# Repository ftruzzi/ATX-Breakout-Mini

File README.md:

ATX Breakout Board
=================

Eagle files for my ATX Breakout Board (v1, with USB support using a TPS2513 and voltage control with a LM317). Based on the Dangerous Prototypes' idea.

## New version (v1.2) ##

<p align="center">
  
</p>

Just finished updating the board. BOM updates and post blogs will follow. I'm also printing a second batch (20-30 PCBs) soon.

Changes and additions:

*   Thickened many traces, **removed pin headers** in the middle of the board and **added one behind each binding post** (up to 5 output pins per voltage line, with no risk of burning any traces).
*   **Added resistors to the USB ports (on the back of the board).** You may want to use them for USB identification, as they are cheaper and easier to find than the TPS2513. Adafruit link for more info: https://learn.adafruit.com/minty-boost/icharging
*   Moved LM317 so that you can mount it horizontally + used a footprint with longpads, should you want to solder wires to an external voltage reg + heatsink.
*   **Prototyping area added** at the top left of the board. Not sure if it will ever come useful, but I had some empty space there. You have easy access to the 3V3 and 5V lines.
*   Moved/rearranged several parts (pot, switch, LEDs) in order to draw shorter and cleaner traces.

##Features

*   **24-pin ATX** connector.
*   Voltage lines are all broken out individually on **binding posts**.
*   **LM317-based voltage regulator**. Using a 300 ohm resistor and a 2K ohm potentiometer, voltage range is 1.25-9V.
*   **2 USB ports **based on the TPS2513 from Texas Instruments. They can automatically detect what device is connected and adjust resistance on D+ and D- lines as needed. This means **full compatibility and maximum charging speed on both Apple and Android devices**. One of them is connected to 5v_STDBY, so that it works even when the PSU is off.
*   Pretty much everything can be **fused**. I left -12V out because it can only carry low amounts of current on most PSUs (mine is 500mA maximum).
*   **Breadboard pin headers** so that voltage lines can be connected to a breadboard using jumper cables.
*   **Voltmeter** headers in order to know the LM317 output voltage.
*   There is room for a **9W power resistor** is your PSU needs it to stabilize output voltages. You can connect it either to the 5v rail or to the 12v one by jumpering the corresponding pads.
*   **Status LEDs** on fused lines and USBs so you can check if everything works fine.
*   Screw holes for standoffs.

More details and pictures on my blog: http://b.truzzi.me/building-a-better-breakout-board-for-atx-psus-2

Suggestions and feedback are very welcome!

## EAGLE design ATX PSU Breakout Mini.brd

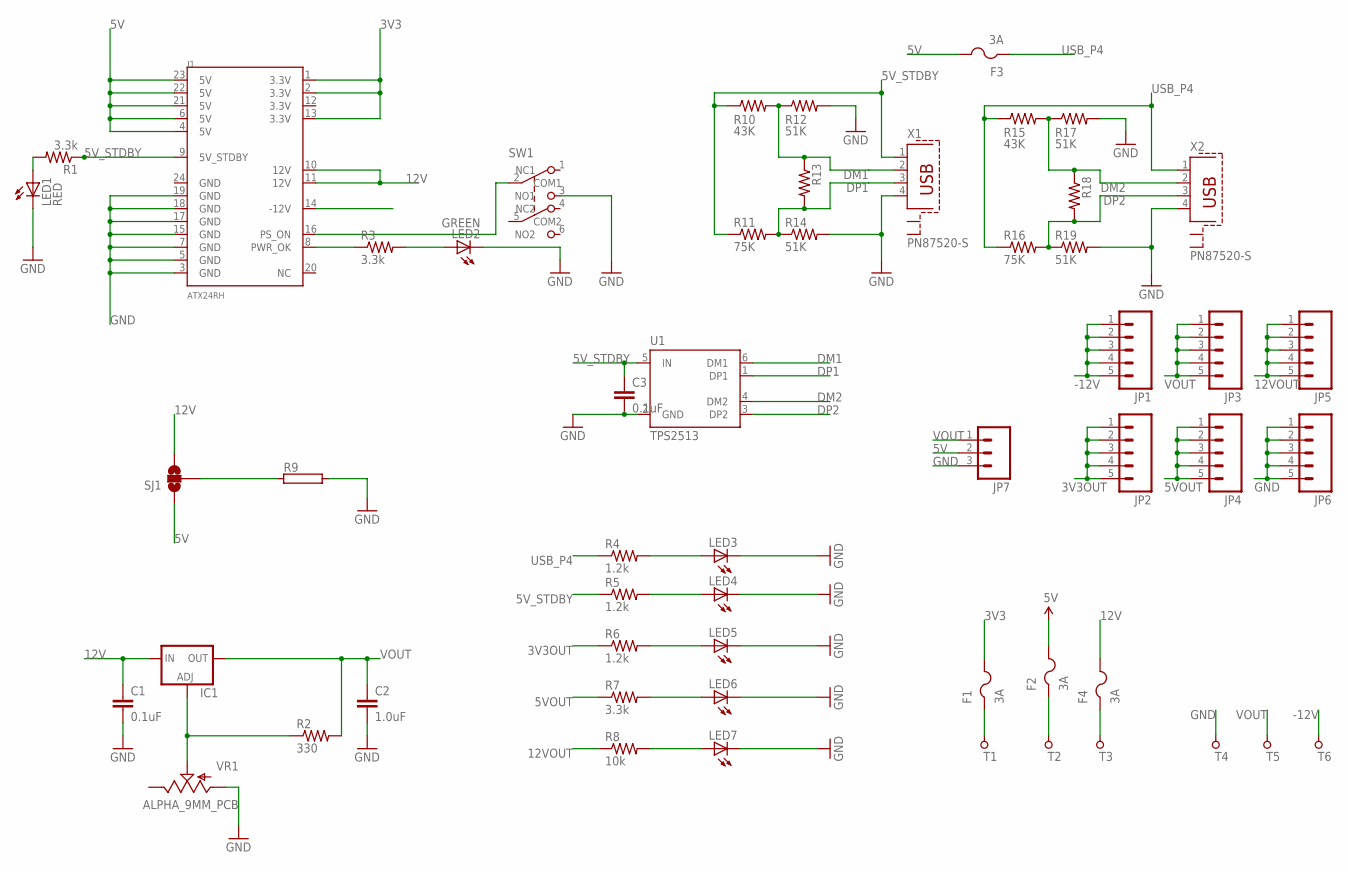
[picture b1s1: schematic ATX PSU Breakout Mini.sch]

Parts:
C1, C3: 0.1uF; 0805
C2: 1.0uF; 0805
F1, F2, F3, F4: 3A; 1812
IC1: LM317TL; 317TL
J1: ATX24RH; ATX24_RIGHT_ANGLE
JP1, JP2, JP3, JP4, JP5, JP6: M05PTH; 1X05
JP7: M03LOCK; 1X03_LOCK
LED1: RED; CHIPLED_0805
LED2: GREEN; CHIPLED_0805
LED3, LED4, LED5, LED6, LED7: LEDCHIPLED_0805; CHIPLED_0805
R1, R3, R7: 3.3k; 0805
R2: 330; 0805
R4, R5, R6: 1.2k; 0805
R8: 10k; 0805
R9: RKH214-8; KH214-8
R10, R15: 43K; 0805
R11, R16: 75K; 0805
R12, R14, R17, R19: 51K; 0805
R13, R18: RESISTOR0805-RES; 0805
SJ1: SOLDERJUMPER_2WAYS; SJ_3
SW1: SW_PUSH_DPDT; SW_PUSH_BUTTON_MINI
T1: 3V3; PAD_ROUND_4.1MM
T2: 5V; PAD_ROUND_4.1MM
T3: 12V; PAD_ROUND_4.1MM
T4: GND; PAD_ROUND_4.1MM
T5: ADJ; PAD_ROUND_4.1MM
T6: -12V; PAD_ROUND_4.1MM
U1: TPS2513; SOT23-6
VR1: ALPHA_9MM_PCB
X1, X2: PN87520-S

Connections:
3V3: F1.2, J1.1 (3.3V), J1.2 (3.3V), J1.13 (3.3V)
3V3OUT: F1.1, JP2.1, JP2.2, JP2.3, JP2.4, JP2.5, R6.1, T1.P
5V: F2.2, F3.2, J1.4 (5V), J1.6 (5V), J1.21 (5V), J1.22 (5V), J1.23 (5V), JP7.2, SJ1.1
5VOUT: F2.1, JP4.1, JP4.2, JP4.3, JP4.4, JP4.5, R7.1, T2.P
5V_STDBY: C3.1, J1.9 (5V_STDBY), R1.1, R5.1, R10.1, R11.1, U1.5 (IN), X1.1
12V: C1.1, F4.2, IC1.3 (IN), J1.10 (12V), J1.11 (12V), SJ1.3
12VOUT: F4.1, JP5.1, JP5.2, JP5.3, JP5.4, JP5.5, R8.1, T3.P
-12V: J1.14 (-12V), JP1.1, JP1.2, JP1.3, JP1.4, JP1.5, T6.P
DM1: R10.2, R12.1, R13.1, U1.6 (DM1), X1.2
DM2: R15.2, R17.1, R18.1, U1.4 (DM2), X2.2
DP1: R11.2, R13.2, R14.1, U1.1 (DP1), X1.3
DP2: R16.2, R18.2, R19.1, U1.3 (DP2), X2.3
GND: C1.2, C2.2, C3.2, J1.3 (GND), J1.5 (GND), J1.7 (GND), J1.15 (GND), J1.17 (GND), J1.18 (GND), J1.19 (GND), JP6.1, JP6.2, JP6.3, JP6.4, JP6.5, JP7.3, LED1.C, LED2.C, LED3.C, LED4.C, LED5.C, LED6.C, LED7.C, R9.2, R12.2, R14.2, R17.2, R19.2, SW1.3 (NO1), T4.P, U1.2 (GND), VR1.1 (A), X1.4, X2.4
unnamed: J1.8 (PWR_OK), R3.1
unnamed: LED2.A, R3.2
unnamed: R9.1, SJ1.2
unnamed: IC1.1 (ADJ), R2.1, VR1.2 (S)
unnamed: J1.16 (PS_ON), SW1.2 (COM1)
unnamed: LED1.A, R1.2
unnamed: LED4.A, R5.2
unnamed: LED3.A, R4.2
unnamed: LED5.A, R6.2
unnamed: LED6.A, R7.2
unnamed: LED7.A, R8.2
USB_P4: F3.1, R4.1, R15.1, R16.1, X2.1
VOUT: C2.1, IC1.2 (OUT), JP3.1, JP3.2, JP3.3, JP3.4, JP3.5, JP7.1, R2.2, T5.P

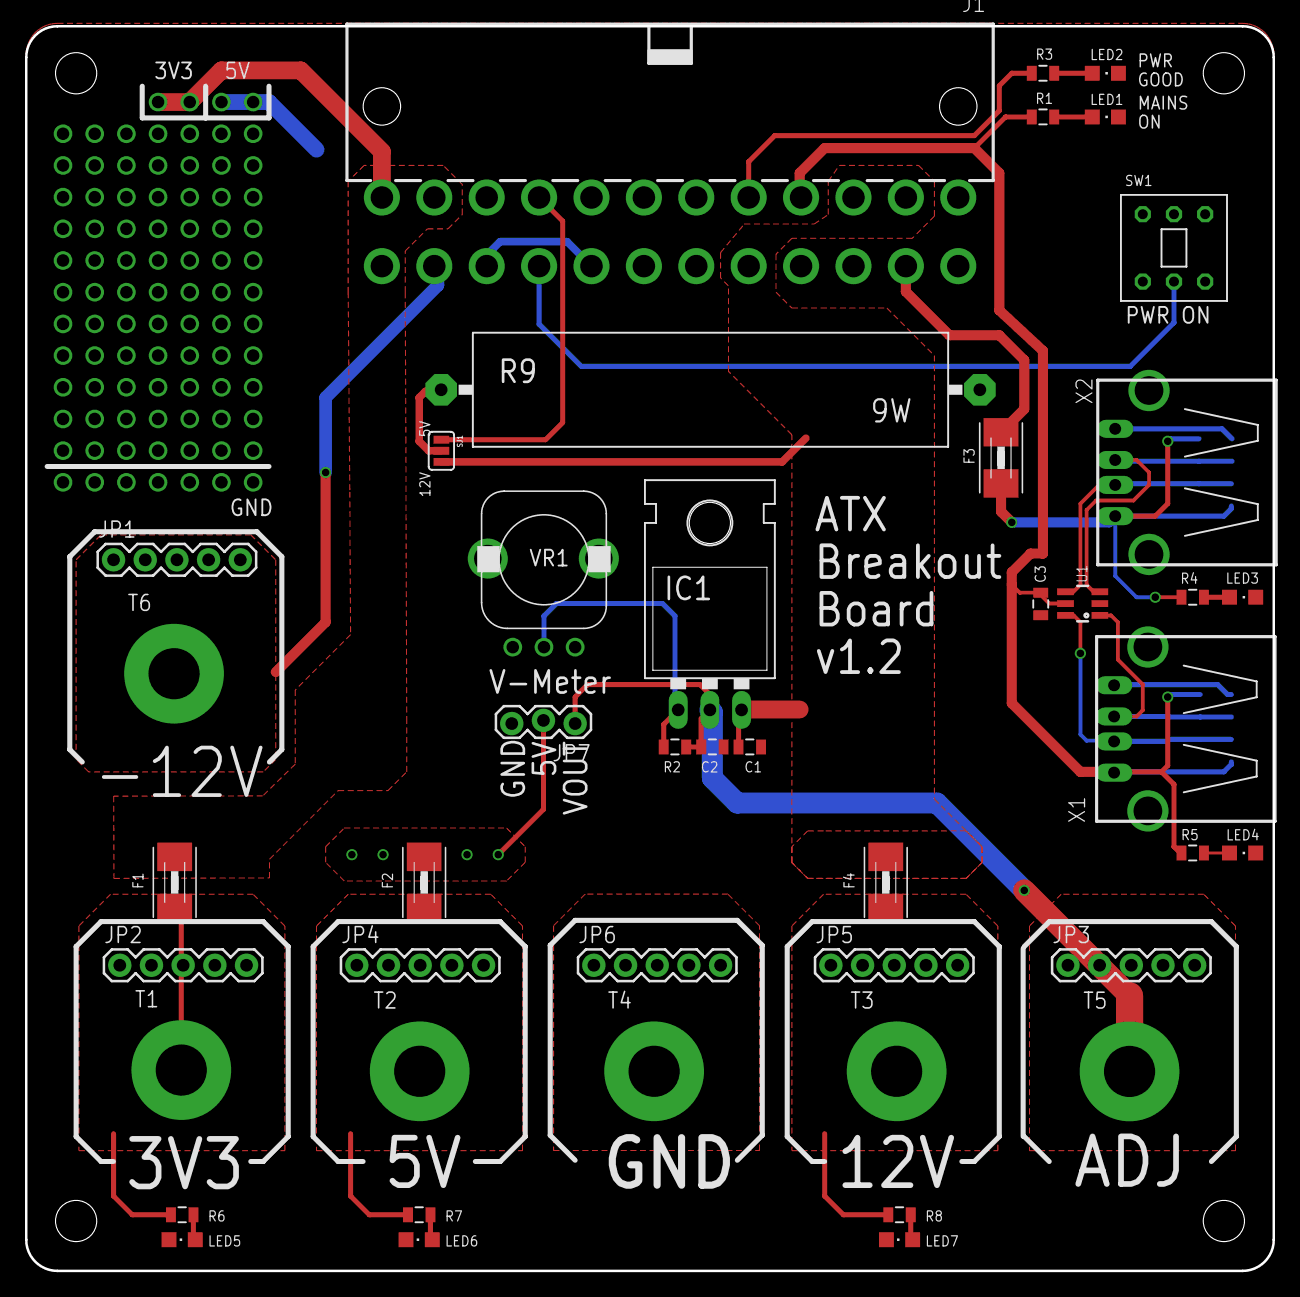
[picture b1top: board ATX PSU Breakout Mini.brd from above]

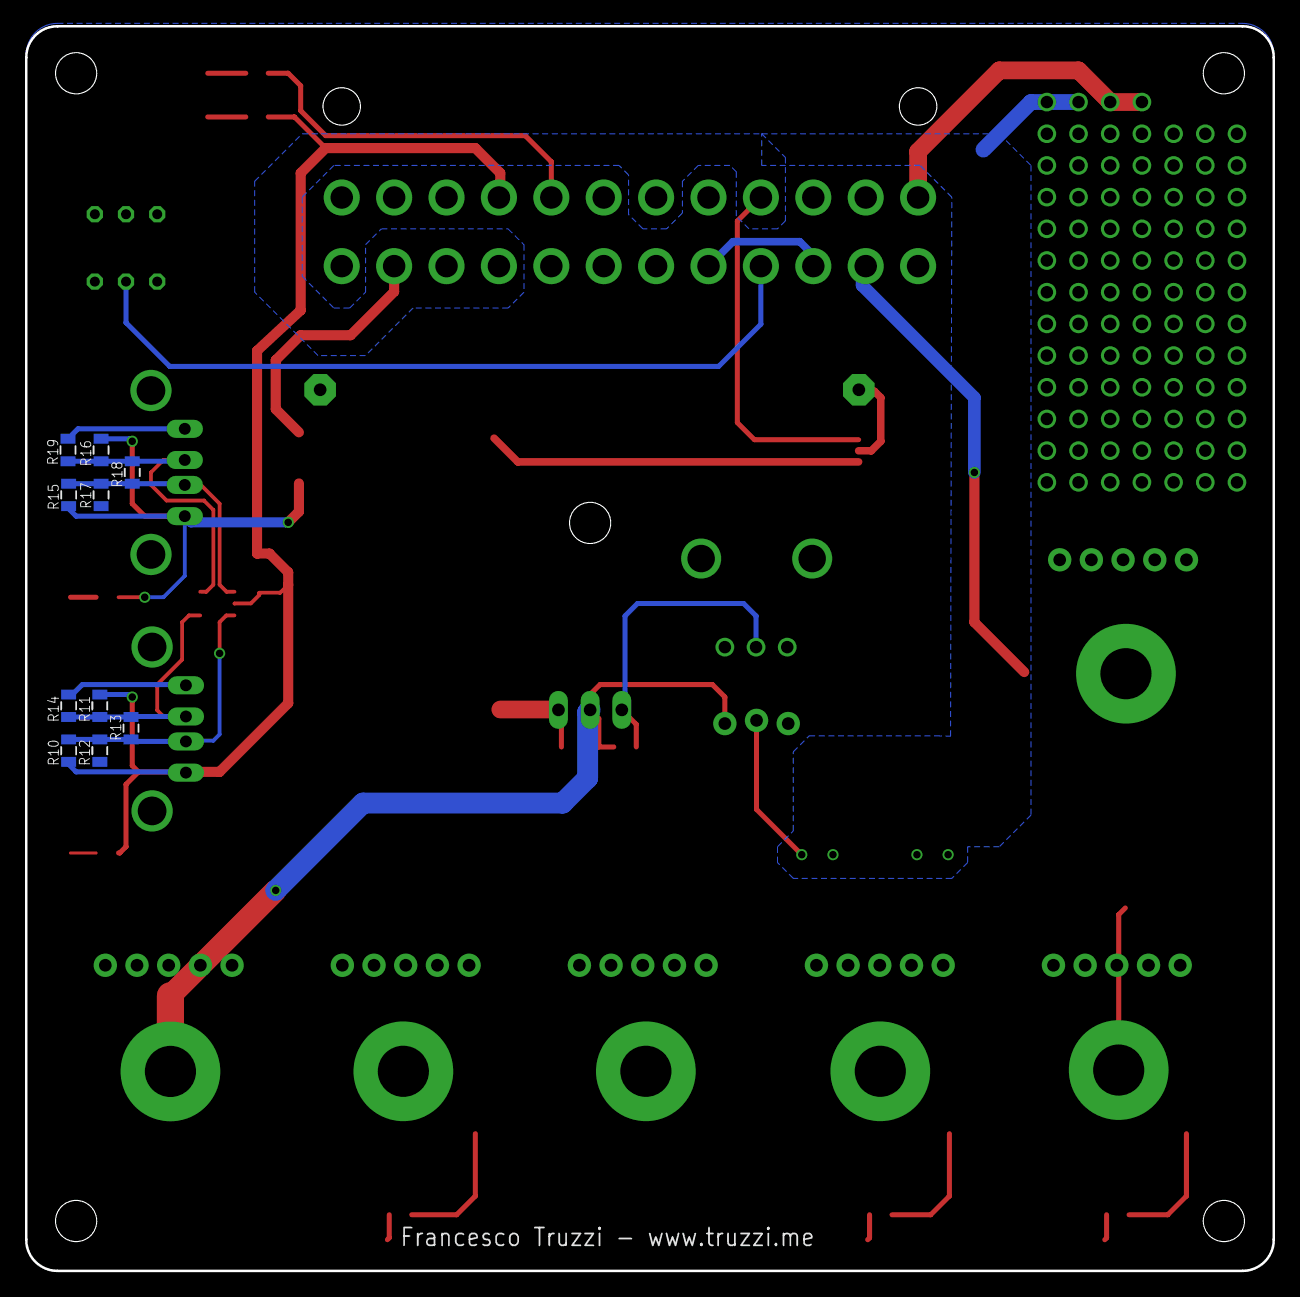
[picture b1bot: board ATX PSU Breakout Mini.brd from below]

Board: 2 copper layers, 100.0 x 99.8 mm, 58 parts (10 on the bottom side), 26 nets.

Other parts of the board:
U$1, U$2, U$3, U$4: STAND-OFF

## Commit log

2014-11-28 first version, eagle files
2015-02-06 Fixes and additions.
    Thickened all traces, added resistors to the USB ports (you can use them
    instead of the TPS2513)
2015-05-30 New version (v1.2)
    Fixed bugs, rearranged traces and components, added pin headers, USB
    resistors and prototyping area.

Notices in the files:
ATX PSU Breakout Mini.sch:
LICENSE: Released under CC BY-NC-SA 4.0
parts and their libraries:
SparkFun-Connectors: Licensing: Creative Commons ShareAlike 4.0 International - https://creativecommons.org/licenses/by-sa/4.0
